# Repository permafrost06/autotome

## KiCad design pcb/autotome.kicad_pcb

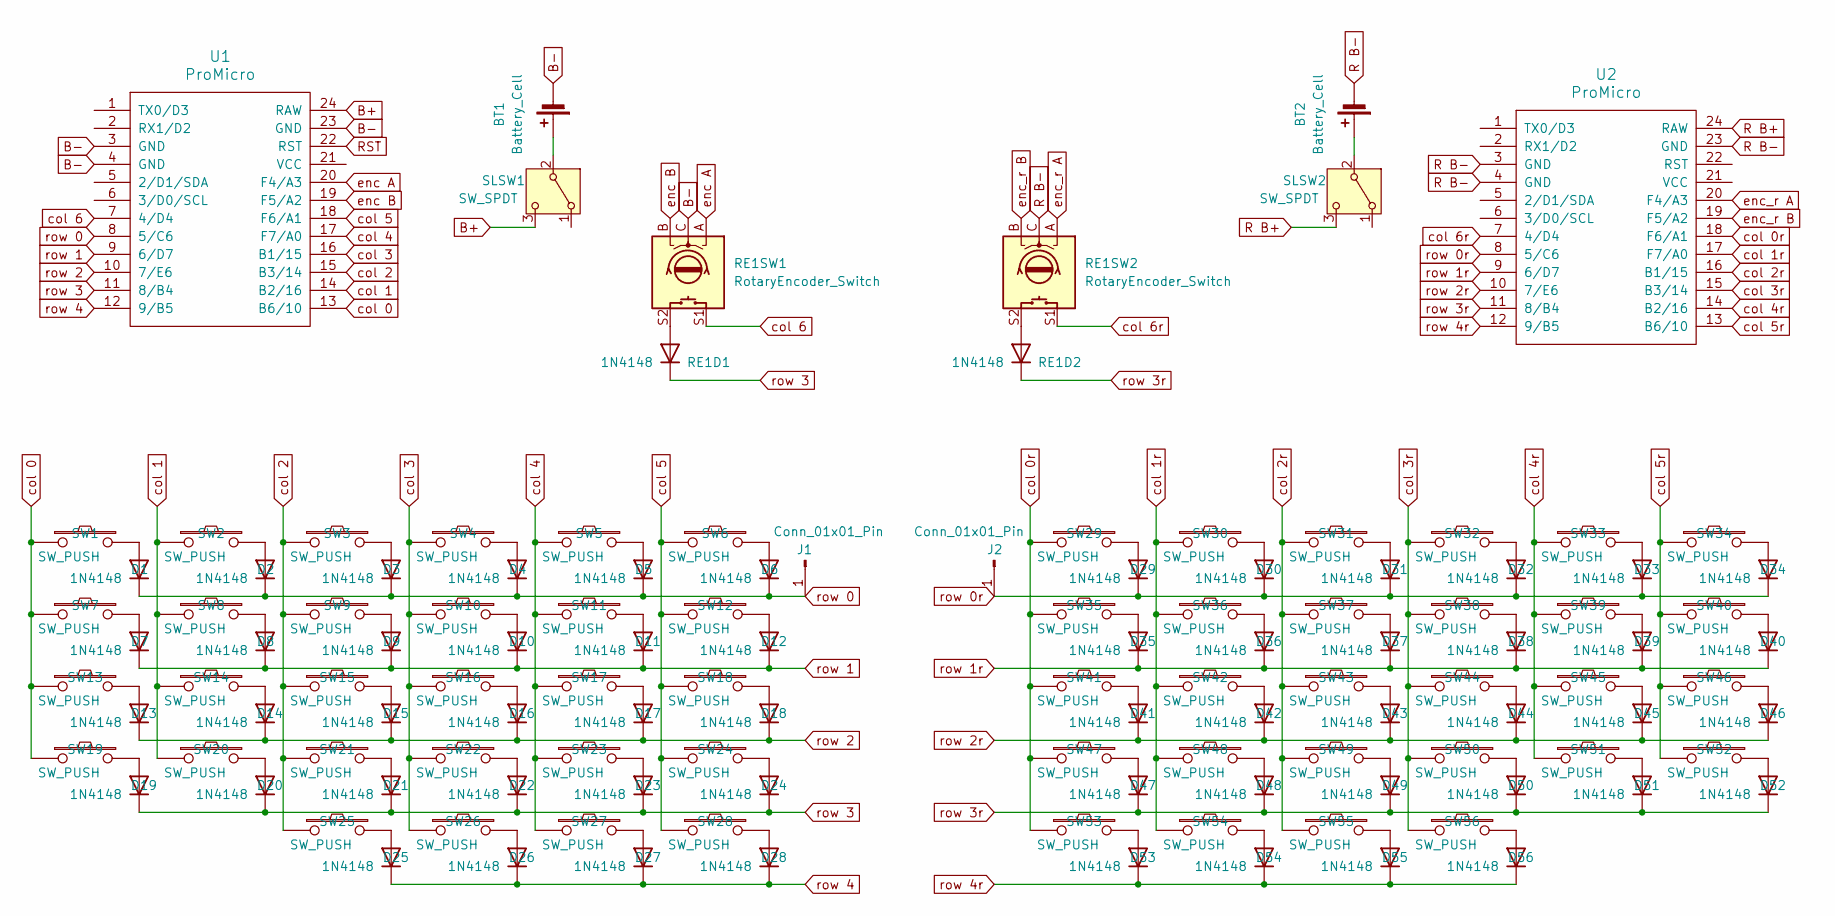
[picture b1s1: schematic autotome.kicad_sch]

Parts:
BT1, BT2: Battery_Cell; JST_XH_B2B-XH-A_1x02_P2.50mm_Vertical
D1, D2, D3, D4, D5, D6, D7, D8, D9, D10, D11, D12, D13, D14, D15, D16, D17, D18, D19, D20, D21, D22, D23, D24, D25, D26, D27, D28, D29, D30, D31, D32, D33, D34, D35, D36, D37, D38, D39, D40, D41, D42, D43, D44, D45, D46, D47, D48, D49, D50, D51, D52, D53, D54, D55, D56: 1N4148; D_DO-35_SOD27_P7.62mm_Horizontal
J1, J2: Conn_01x01_Pin; TestPoint_THTPad_1.0x1.0mm_Drill0.5mm
RE1D1, RE1D2: 1N4148; D_DO-35_SOD27_P7.62mm_Horizontal
RE1SW1, RE1SW2: RotaryEncoder_Switch; RotaryEncoder_Alps_EC11E-Switch_Vertical_H20mm
SLSW1, SLSW2: SW_SPDT; SW_Slide_SPDT_Straight_CK_OS102011MS2Q
SW1, SW2, SW3, SW4, SW5, SW6, SW7, SW8, SW9, SW10, SW11, SW12, SW13, SW14, SW15, SW16, SW17, SW18, SW19, SW20, SW21, SW22, SW23, SW24, SW25, SW26, SW27, SW28, SW29, SW30, SW31, SW32, SW33, SW34, SW35, SW36, SW37, SW38, SW39, SW40, SW41, SW42, SW43, SW44, SW45, SW46, SW47, SW48, SW49, SW50, SW51, SW52, SW53, SW54, SW55, SW56: SW_PUSH; SW_Hotswap_Kailh_MX_Plated_1.00u
U1, U2: ProMicro; NiceNano

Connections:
B+: SLSW1.3 (C), U1.24 (RAW)
B-: BT1.2 (-), RE1SW1.C, U1.3 (GND), U1.4 (GND), U1.23 (GND)
unnamed: BT1.1 (+), SLSW1.2 (B)
unnamed: BT2.1 (+), SLSW2.2 (B)
unnamed: D1.2 (A), SW1.2
unnamed: D2.2 (A), SW2.2
unnamed: D3.2 (A), SW3.2
unnamed: D4.2 (A), SW4.2
unnamed: D5.2 (A), SW5.2
unnamed: D6.2 (A), SW6.2
unnamed: D7.2 (A), SW7.2
unnamed: D8.2 (A), SW8.2
unnamed: D9.2 (A), SW9.2
unnamed: D10.2 (A), SW10.2
unnamed: D11.2 (A), SW11.2
unnamed: D12.2 (A), SW12.2
unnamed: D13.2 (A), SW13.2
unnamed: D14.2 (A), SW14.2
unnamed: D15.2 (A), SW15.2
unnamed: D16.2 (A), SW16.2
unnamed: D17.2 (A), SW17.2
unnamed: D18.2 (A), SW18.2
unnamed: D19.2 (A), SW19.2
unnamed: D20.2 (A), SW20.2
unnamed: D21.2 (A), SW21.2
unnamed: D22.2 (A), SW22.2
unnamed: D23.2 (A), SW23.2
unnamed: D24.2 (A), SW24.2
unnamed: D25.2 (A), SW25.2
unnamed: D26.2 (A), SW26.2
unnamed: D27.2 (A), SW27.2
unnamed: D28.2 (A), SW28.2
unnamed: D29.2 (A), SW29.2
unnamed: D30.2 (A), SW30.2
unnamed: D31.2 (A), SW31.2
unnamed: D32.2 (A), SW32.2
unnamed: D33.2 (A), SW33.2
unnamed: D34.2 (A), SW34.2
unnamed: D35.2 (A), SW35.2
unnamed: D36.2 (A), SW36.2
unnamed: D37.2 (A), SW37.2
unnamed: D38.2 (A), SW38.2
unnamed: D39.2 (A), SW39.2
unnamed: D40.2 (A), SW40.2
unnamed: D41.2 (A), SW41.2
unnamed: D42.2 (A), SW42.2
unnamed: D43.2 (A), SW43.2
unnamed: D44.2 (A), SW44.2
unnamed: D45.2 (A), SW45.2
unnamed: D46.2 (A), SW46.2
unnamed: D47.2 (A), SW47.2
unnamed: D48.2 (A), SW48.2
unnamed: D49.2 (A), SW49.2
unnamed: D50.2 (A), SW50.2
unnamed: D51.2 (A), SW51.2
unnamed: D52.2 (A), SW52.2
unnamed: D53.2 (A), SW53.2
unnamed: D54.2 (A), SW54.2
unnamed: D55.2 (A), SW55.2
unnamed: D56.2 (A), SW56.2
unnamed: RE1D1.2 (A), RE1SW1.S2
unnamed: RE1D2.2 (A), RE1SW2.S2
R B+: SLSW2.3 (C), U2.24 (RAW)
R B-: BT2.2 (-), RE1SW2.C, U2.3 (GND), U2.4 (GND), U2.23 (GND)
RST: U1.22 (RST)
col 0: SW1.1, SW7.1, SW13.1, SW19.1, U1.13 (B6/10)
col 0r: SW29.1, SW35.1, SW41.1, SW47.1, SW53.1, U2.18 (F6/A1)
col 1: SW2.1, SW8.1, SW14.1, SW20.1, U1.14 (B2/16)
col 1r: SW30.1, SW36.1, SW42.1, SW48.1, SW54.1, U2.17 (F7/A0)
col 2: SW3.1, SW9.1, SW15.1, SW21.1, SW25.1, U1.15 (B3/14)
col 2r: SW31.1, SW37.1, SW43.1, SW49.1, SW55.1, U2.16 (B1/15)
col 3: SW4.1, SW10.1, SW16.1, SW22.1, SW26.1, U1.16 (B1/15)
col 3r: SW32.1, SW38.1, SW44.1, SW50.1, SW56.1, U2.15 (B3/14)
col 4: SW5.1, SW11.1, SW17.1, SW23.1, SW27.1, U1.17 (F7/A0)
col 4r: SW33.1, SW39.1, SW45.1, SW51.1, U2.14 (B2/16)
col 5: SW6.1, SW12.1, SW18.1, SW24.1, SW28.1, U1.18 (F6/A1)
col 5r: SW34.1, SW40.1, SW46.1, SW52.1, U2.13 (B6/10)
col 6: RE1SW1.S1, U1.7 (4/D4)
col 6r: RE1SW2.S1, U2.7 (4/D4)
enc A: RE1SW1.A, U1.20 (F4/A3)
enc B: RE1SW1.B, U1.19 (F5/A2)
enc_r A: RE1SW2.A, U2.20 (F4/A3)
enc_r B: RE1SW2.B, U2.19 (F5/A2)
row 0: D1.1 (K), D2.1 (K), D3.1 (K), D4.1 (K), D5.1 (K), D6.1 (K), J1.1 (Pin_1_1), U1.8 (5/C6)
row 0r: D29.1 (K), D30.1 (K), D31.1 (K), D32.1 (K), D33.1 (K), D34.1 (K), J2.1 (Pin_1_1), U2.8 (5/C6)
row 1: D7.1 (K), D8.1 (K), D9.1 (K), D10.1 (K), D11.1 (K), D12.1 (K), U1.9 (6/D7)
row 1r: D35.1 (K), D36.1 (K), D37.1 (K), D38.1 (K), D39.1 (K), D40.1 (K), U2.9 (6/D7)
row 2: D13.1 (K), D14.1 (K), D15.1 (K), D16.1 (K), D17.1 (K), D18.1 (K), U1.10 (7/E6)
row 2r: D41.1 (K), D42.1 (K), D43.1 (K), D44.1 (K), D45.1 (K), D46.1 (K), U2.10 (7/E6)
row 3: D19.1 (K), D20.1 (K), D21.1 (K), D22.1 (K), D23.1 (K), D24.1 (K), RE1D1.1 (K), U1.11 (8/B4)
row 3r: D47.1 (K), D48.1 (K), D49.1 (K), D50.1 (K), D51.1 (K), D52.1 (K), RE1D2.1 (K), U2.11 (8/B4)
row 4: D25.1 (K), D26.1 (K), D27.1 (K), D28.1 (K), U1.12 (9/B5)
row 4r: D53.1 (K), D54.1 (K), D55.1 (K), D56.1 (K), U2.12 (9/B5)

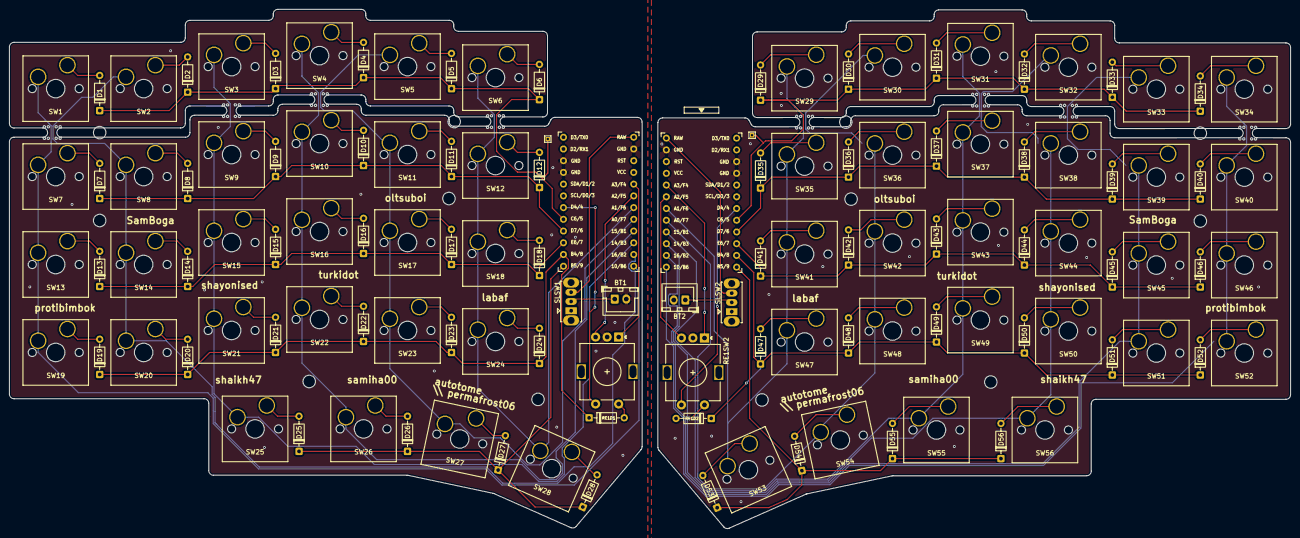
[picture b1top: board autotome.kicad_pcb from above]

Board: 2 copper layers, 277.5 x 112.4 mm, 124 parts (1 on the bottom side), 92 nets.

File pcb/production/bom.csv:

Designator,Footprint,Quantity,Value,LCSC Part #
"BT1, BT2",JST_XH_B2B-XH-A_1x02_P2.50mm_Vertical,2,Battery_Cell,
"D1, D10, D11, D12, D13, D14, D15, D16, D17, D18, D19, D2, D20, D21, D22, D23, D24, D25, D26, D27, D28, D29, D3, D30, D31, D32, D33, D34, D35, D36, D37, D38, D39, D4, D40, D41, D42, D43, D44, D45, D46, D47, D48, D49, D5, D50, D51, D52, D53, D54, D55, D56, D6, D7, D8, D9, RE1D1, RE1D2",D_DO-35_SOD27_P7.62mm_Horizontal,58,1N4148,
"RE1SW1, RE1SW2",RotaryEncoder_Alps_EC11E-Switch_Vertical_H20mm,2,RotaryEncoder_Switch,
"SLSW1, SLSW2",SW_Slide_SPDT_Straight_CK_OS102011MS2Q,2,SW_SPDT,
"SW1, SW10, SW11, SW12, SW13, SW14, SW15, SW16, SW17, SW18, SW19, SW2, SW20, SW21, SW22, SW23, SW24, SW25, SW26, SW27, SW28, SW29, SW3, SW30, SW31, SW32, SW33, SW34, SW35, SW36, SW37, SW38, SW39, SW4, SW40, SW41, SW42, SW43, SW44, SW45, SW46, SW47, SW48, SW49, SW5, SW50, SW51, SW52, SW53, SW54, SW55, SW56, SW6, SW7, SW8, SW9",SW_Hotswap_Kailh_MX_Plated_1.00u,56,SW_PUSH,
"U1, U2",NiceNano,2,ProMicro,

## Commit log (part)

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2026-06-15 trying to make encoder work
2026-06-16 fix bottom row
2026-06-16 fix bottom row column mappings
2026-06-17 split encoder bindings
2026-06-17 add zmk studio support
2026-06-23 add missing workflows
2026-06-23 remove zmk studio from build
2026-06-23 re-enable zmk studio
2026-06-23 try to fix build with zmk studio
2026-06-23 change right half hmrs to be right modifiers instead of left
2026-06-24 change keyboard name to autotome
